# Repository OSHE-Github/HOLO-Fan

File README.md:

# HOLO-Fan
This project is about designing and building an open-source holographic display fan for outreach events and educational demonstration.

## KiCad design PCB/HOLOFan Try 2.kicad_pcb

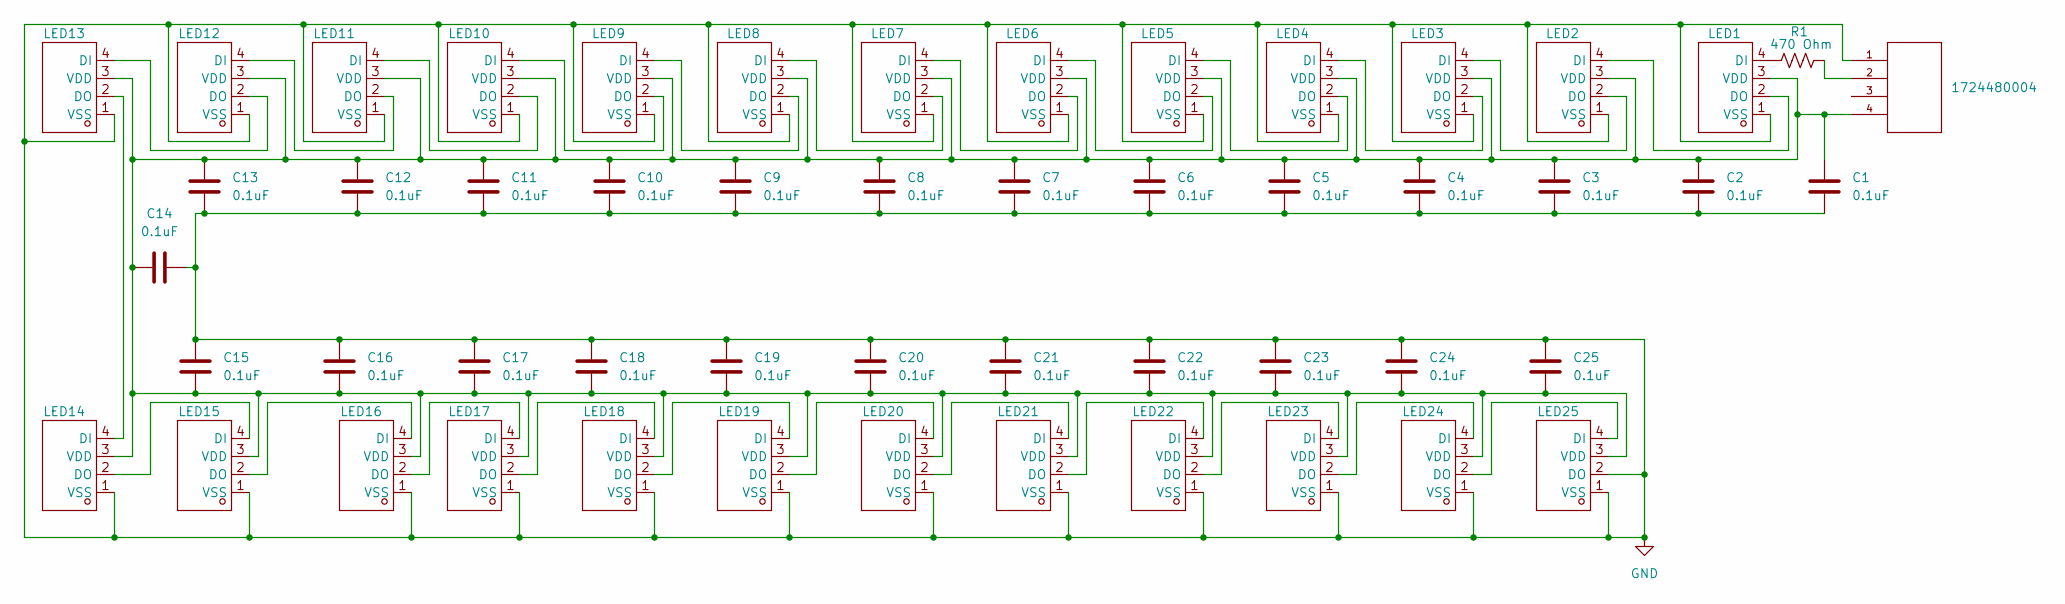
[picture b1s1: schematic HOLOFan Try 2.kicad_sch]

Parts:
C1, C2, C3, C4, C5, C6, C7, C8, C9, C10, C11, C12, C13, C14, C15, C16, C17, C18, C19, C20, C21, C22, C23, C24, C25: 0.1uF; C_0603_1608Metric_Pad1.08x0.95mm_HandSolder; JLCPCB PART CLASS CL10B104KA8NNNC
J1: 1724480004; CONN_SD-172448-0000_04_MOL; MANUFACTURER_PART_NUMBER 1724480004
LED1, LED2, LED3, LED4, LED5, LED6, LED7, LED8, LED9, LED10, LED11, LED12, LED13, LED14, LED15, LED16, LED17, LED18, LED19, LED20, LED21, LED22, LED23, LED24, LED25: xl-4020rgbc-2812b; LED-SMD_4P-L4.0-W1.7_XL-4020RGBC-WS2812B; VOLTAGE - SUPPLY 4.5V~5.5V; MANUFACTURERPART XL-4020RGBC-2812B; LCSC PART NAME XL-4020RGBC-WS2812B
R1: 470 Ohm; R_Axial_DIN0207_L6.3mm_D2.5mm_P7.62mm_Horizontal

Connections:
GND: C1.2, C2.2, C3.2, C4.2, C5.2, C6.2, C7.2, C8.2, C9.2, C10.2, C11.2, C12.2, C13.2, C14.1, C15.1, C16.1, C17.1, C18.1, C19.1, C20.1, C21.1, C22.1, C23.1, C24.1, C25.1, J1.1, LED1.1 (VSS), LED2.1 (VSS), LED3.1 (VSS), LED4.1 (VSS), LED5.1 (VSS), LED6.1 (VSS), LED7.1 (VSS), LED8.1 (VSS), LED9.1 (VSS), LED10.1 (VSS), LED11.1 (VSS), LED12.1 (VSS), LED13.1 (VSS), LED14.1 (VSS), LED15.1 (VSS), LED16.1 (VSS), LED17.1 (VSS), LED18.1 (VSS), LED19.1 (VSS), LED20.1 (VSS), LED21.1 (VSS), LED22.1 (VSS), LED23.1 (VSS), LED24.1 (VSS), LED25.1 (VSS), LED25.2 (DO)
unnamed: J1.2, R1.2
unnamed: LED1.4 (DI), R1.1
unnamed: LED1.2 (DO), LED2.4 (DI)
unnamed: C1.1, C2.1, C3.1, C4.1, C5.1, C6.1, C7.1, C8.1, C9.1, C10.1, C11.1, C12.1, C13.1, C14.2, C15.2, C16.2, C17.2, C18.2, C19.2, C20.2, C21.2, C22.2, C23.2, C24.2, C25.2, J1.4, LED1.3 (VDD), LED2.3 (VDD), LED3.3 (VDD), LED4.3 (VDD), LED5.3 (VDD), LED6.3 (VDD), LED7.3 (VDD), LED8.3 (VDD), LED9.3 (VDD), LED10.3 (VDD), LED11.3 (VDD), LED12.3 (VDD), LED13.3 (VDD), LED14.3 (VDD), LED15.3 (VDD), LED16.3 (VDD), LED17.3 (VDD), LED18.3 (VDD), LED19.3 (VDD), LED20.3 (VDD), LED21.3 (VDD), LED22.3 (VDD), LED23.3 (VDD), LED24.3 (VDD), LED25.3 (VDD)
unnamed: LED2.2 (DO), LED3.4 (DI)
unnamed: LED3.2 (DO), LED4.4 (DI)
unnamed: LED4.2 (DO), LED5.4 (DI)
unnamed: LED5.2 (DO), LED6.4 (DI)
unnamed: LED6.2 (DO), LED7.4 (DI)
unnamed: LED7.2 (DO), LED8.4 (DI)
unnamed: LED8.2 (DO), LED9.4 (DI)
unnamed: LED9.2 (DO), LED10.4 (DI)
unnamed: LED10.2 (DO), LED11.4 (DI)
unnamed: LED11.2 (DO), LED12.4 (DI)
unnamed: LED12.2 (DO), LED13.4 (DI)
unnamed: LED13.2 (DO), LED14.4 (DI)
unnamed: LED14.2 (DO), LED15.4 (DI)
unnamed: LED15.2 (DO), LED16.4 (DI)
unnamed: LED16.2 (DO), LED17.4 (DI)
unnamed: LED17.2 (DO), LED18.4 (DI)
unnamed: LED18.2 (DO), LED19.4 (DI)
unnamed: LED19.2 (DO), LED20.4 (DI)
unnamed: LED20.2 (DO), LED21.4 (DI)
unnamed: LED21.2 (DO), LED22.4 (DI)
unnamed: LED22.2 (DO), LED23.4 (DI)
unnamed: LED23.2 (DO), LED24.4 (DI)
unnamed: LED24.2 (DO), LED25.4 (DI)

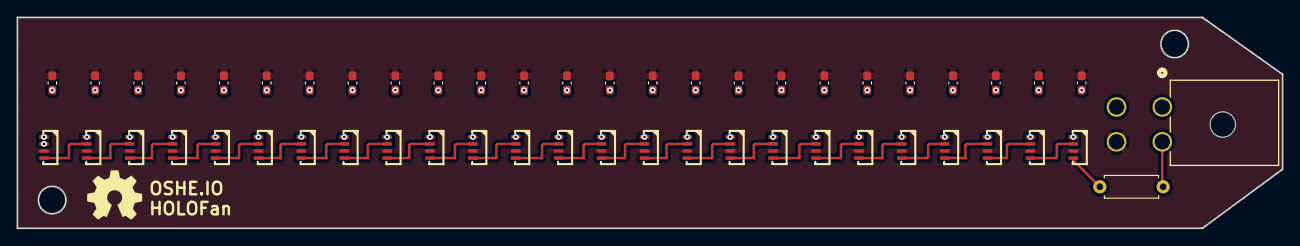
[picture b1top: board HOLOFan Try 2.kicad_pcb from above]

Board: 2 copper layers, 152.4 x 25.4 mm, 52 parts (0 on the bottom side), 28 nets.

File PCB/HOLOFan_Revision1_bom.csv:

Designator,Footprint,Quantity,Value,LCSC Part #
"C1, C10, C11, C12, C13, C14, C15, C16, C17, C18, C19, C2, C20, C21, C22, C23, C24, C25, C3, C4, C5, C6, C7, C8, C9",0603,25,0.1uF,C1590
"LED1, LED10, LED11, LED12, LED13, LED14, LED15, LED16, LED17, LED18, LED19, LED2, LED20, LED21, LED22, LED23, LED24, LED25, LED3, LED4, LED5, LED6, LED7, LED8, LED9",LED-SMD_4P-L4.0-W1.7_XL-4020RGBC-WS2812B,25,xl-4020rgbc-2812b,C3647024
